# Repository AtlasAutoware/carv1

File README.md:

# carv1 — Atlas Autoware's first car

Everything for Atlas Autoware's first 1/10-scale autonomous race car in one
repo: the ROS 2 racing software, the Jetson setup that runs it, and the CAD
and electronics for the physical build. (The next car lives in
[carv2](https://github.com/AtlasAutoware/carv2).)

This repo combines two earlier ones, with their full commit history:
`atlasautoware` (the software, now the repo root) and `atlasautoware-cad`
(now [`cad/`](cad/)).

## What's where

| Path | What it holds |
|---|---|
| `f1tenth_gym_ros/`, `launch/`, `config/` | The ROS 2 racing stack: nodes, launch files, sim and car parameters |
| `racelines/`, `maps/` | Optimized racelines and track maps |
| `tools/`, `tests/`, `ui/`, `ml/`, `models/` | Tuning and benchmarking scripts, tests, the live dashboard, perception models |
| `hardware/` | What runs on the Jetson outside the ROS package: bringup scripts, udev rules, VESC config, race-day [RUNBOOK](hardware/RUNBOOK.md) |
| `docs/` | Design notes (MPC, racing tech, mapping, hardware wiring) and the project paper/report |
| `cad/Components/` | 3D models of the off-the-shelf parts (Jetson Orin Nano, RPLIDAR C1, PCA9685) |
| `cad/Mounts/` | Scripted (CadQuery) mounts and baseplate, with fit checks, fab exports and G-code — see [DESIGN.md](cad/Mounts/DESIGN.md) |
| `cad/Templates/` | The original clipless mounting system and baseplate the mounts are built on |
| `cad/Electronics/` | AtlasPower-4S, the power board that runs the car's electronics off the 4S drive pack — see its [README](cad/Electronics/README.md) |
| `cad/Jetson/` | JetPack rebuild and smoke-test scripts |

## The software stack

A complete ROS 2 racing stack for 1/10-scale autonomous racing: simulation
bridge, SLAM mapping, raceline optimization, an OSQP-based MPC racing
controller with lidar AEB and an IMU traction governor, camera opponent
detection, and a hardware bringup layer (Jetson + OAK-D Pro + RPLidar + VESC)
so the same nodes that win in sim drive the physical car.

Built on the [f1tenth_gym_ros](https://github.com/f1tenth/f1tenth_gym_ros)
simulation bridge (ROS 2 Humble).

```
                 ┌── sim:  gym_bridge (f1tenth_gym) ──────────────┐
sensors ─────────┤                                                ├──► /scan, odom, /oakd/*
                 └── car:  rplidar_node · oakd_camera · drive_node┘
                                            ▲
map ─► slam_toolbox ─► raceline_optimizer ─► raceline_mpc (MPC + AEB + traction governor) ─► /drive
                                            │
                       camera_perception ───┘ (YOLO opponent detection, optional)
```

## The racing pipeline

1. **Map** the track: `ros2 launch f1tenth_gym_ros slam_mapping_launch.py`
   driving slowly (or `mapping_driver` autonomously) — see
   [docs/mapping.md](docs/mapping.md).
2. **Optimize** a raceline: `raceline_optimizer` / `track_learner` produce
   `racelines/*.csv` (x, y, heading, curvature, speed); inspect with
   `tools/draw_raceline.py`.
3. **Profile** the speeds: `tools/reprofile_raceline.py` (or
   `reprofile_speeds: true` at runtime) replaces the speed column with the
   TUMFTM friction-limited forward-backward profile, so commanded speeds
   provably fit the grip budget — see
   [docs/racing_tech.md](docs/racing_tech.md).
4. **Race**: `raceline_mpc` tracks the line with a kinematic LTV-MPC
   (persistent warm-started OSQP solve, ~0.6 ms/tick), falls back to the
   MAP controller (Becker et al., ICRA 2023 — tire-aware pursuit) on any
   solver hiccup, brakes for obstacles with a speed-aware AEB, and scales
   speed when the IMU says grip is running out — see
   [docs/mpc.md](docs/mpc.md) and [docs/racing_tech.md](docs/racing_tech.md).

Racing nodes: `raceline_mpc` (competition time-trial), `race_agent` /
`racing_agent` (full strategy + opponents), `opponent_driver`,
`camera_perception` ([docs/camera_perception.md](docs/camera_perception.md)).
Tooling: `tools/auto_tune.py`, `tools/benchmark_lap.py`, and a live dashboard
([docs/dashboard.md](docs/dashboard.md)).

## Quickstart — simulation

Supported: Ubuntu 22.04 native with ROS 2 Humble, or any OS via Docker
(NVIDIA GPU with `rocker`, or noVNC without).

**Native (Ubuntu 22.04 + ROS 2 Humble):**
```bash
# dependencies
git clone https://github.com/f1tenth/f1tenth_gym && cd f1tenth_gym && pip3 install -e . && cd ..
# workspace
mkdir -p $HOME/sim_ws/src && cd $HOME/sim_ws/src
git clone https://github.com/AtlasAutoware/carv1 atlasautoware   # the paths below expect this folder name
# point map_path in config/sim.yaml at <your_home>/sim_ws/src/atlasautoware/maps/levine
cd $HOME/sim_ws
rosdep install -i --from-path src --rosdistro humble -y
colcon build
source /opt/ros/humble/setup.bash && source install/local_setup.bash
ros2 launch f1tenth_gym_ros gym_bridge_launch.py
```

**Docker (NVIDIA GPU):**
```bash
docker build -t f1tenth_gym_ros -f Dockerfile .
rocker --nvidia --x11 --volume .:/sim_ws/src/f1tenth_gym_ros -- f1tenth_gym_ros
```

**Docker (no GPU, noVNC):**
```bash
docker-compose up
# second terminal:
docker exec -it f1tenth_gym_ros-sim-1 /bin/bash
# browser: http://localhost:8080/vnc.html → Connect, then launch as above
```

Use `headless_bridge_launch.py` instead of `gym_bridge_launch.py` for
benchmarking/auto-tuning without rviz.

## Quickstart — real car

Jetson + OAK-D Pro (RGB + 200 Hz IMU) + RPLidar + VESC. Actuation goes
through a PCA9685 PWM board into the VESC's PPM input **or** direct VESC
UART — `drive_node` probes both at startup and uses what it finds:

```bash
pip3 install depthai rplidar-roboticia smbus2 pyserial
ros2 launch f1tenth_gym_ros car_bringup_launch.py
```

Install and compile the optional car detector once on the Jetson, then enable
it in bringup:

```bash
cd ~/atlas_ws/src/atlasautoware
hardware/scripts/install_tensorrt.sh
cd ~/atlas_ws
colcon build --packages-select f1tenth_gym_ros
source install/setup.bash
ros2 launch f1tenth_gym_ros car_bringup_launch.py use_perception:=true
```

Calibration (steering trim, `erpm_gain`, speed scaling) lives in
`config/hardware.yaml`. Wiring, VESC Tool setup, and the first-drive
calibration order are in [docs/hardware.md](docs/hardware.md). Both actuation
paths carry an arming hold, a command watchdog, and neutral-on-shutdown.
YOLO opponent detection uses a device-built TensorRT engine directly on the
Jetson GPU. The ONNX export is only an engine-build input; ONNX Runtime is not
loaded in the car process. See [docs/camera_perception.md](docs/camera_perception.md).

## Configuration

- `config/sim.yaml` — simulation: `map_path`, `num_agent` (1 or 2), start
  poses, `kb_teleop` (then `ros2 run teleop_twist_keyboard
  teleop_twist_keyboard`: `i`/`u`/`o` forward, `,`/`m`/`.` reverse, `k` stop).
- `config/hardware.yaml` — drive backend + sensor + racing parameters for the
  car.
- `config/slam_mapping.yaml` — mapping session settings.

## Topics

| Topic | Type | Direction |
|---|---|---|
| `/scan` | LaserScan | sim bridge / rplidar_node → stack |
| `/ego_racecar/odom` (sim) · `/pf/pose/odom` (car) | Odometry | localization → controllers |
| `/oakd/rgb`, `/oakd/camera_info` | Image, CameraInfo | oakd_camera → camera_perception |
| `/oakd/imu` | Imu | oakd_camera → traction governor |
| `/vesc/odom` | Odometry | drive_node (UART backend) → particle filter |
| `/drive` | AckermannDriveStamped | controllers → sim bridge / drive_node |
| `/map`, `tf` | — | map server / SLAM |

Two-agent sim additionally has `/opp_scan`, `/opp_drive`,
`/opp_racecar/odom`, and mirrored `opp_odom` topics; reset poses via RViz's
*2D Pose Estimate* (`/initialpose`) and *2D Goal Pose* tools.

## Tests

```bash
python3 -m pytest tests/ -q        # pure-logic: MPC, race brain, hardware drivers
python3 tests/test_mpc.py          # closed-loop MPC validation + solve-time budget
```

`tests/test_hardware.py` covers the PCA9685 register/pulse maths, the VESC
UART protocol, drive-backend auto-detection, lidar scan binning, and the
traction governor — no hardware or ROS needed.

## License

MIT — see [LICENSE](LICENSE).

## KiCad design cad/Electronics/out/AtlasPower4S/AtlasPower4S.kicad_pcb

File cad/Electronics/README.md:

# AtlasPower-4S

One board that runs the new car's electronics off the 4S drive LiPo, so the Baseus power
bank and the USB-C PD trigger come off the car entirely. 88 x 68 mm, four M3 holes on a
76 x 56 pattern, mounted on the clipless system by `../cad/power_board_mount.py`.

    XT90 -> 10 A fuse -> TVS -> ideal-diode FET -> 5 mohm shunt -> VIN
    VIN  -> AP64501 -> 10.0 V  Jetson Orin Nano + SICK TiM561
         -> AP64501 ->  7.4 V  INJORA INJS235 servo
         -> AP64501 ->  5.0 V  USB hub, PCA9685, fan
    INA226 across the shunt -> I2C -> Jetson

## Why these numbers

The pack is 12.0 V at a 3.0 V/cell cutoff and 16.8 V full. The Jetson takes 9-20 V and the
TiM561 takes 9-28 V, so both would run straight off the pack, and that is the tempting
wrong answer: the pack rail carries the motor's switching noise, and a hard launch sags it
far enough to brown out the Jetson mid-run.

The compute rail is therefore **10 V, not 12 V**. At 12 V a buck has no headroom left when
the pack is nearly flat and you need a buck-boost, which is a four-switch converter and a
much harder board. At 10 V a plain synchronous buck still has 0.8 V of headroom even at an
11 V sag, which is the single decision that keeps this board simple enough to get right.

Servo peaks are handled by a 470 uF reservoir rather than by sizing the regulator for
stall: a 35 kg-class servo pulls 3-6 A stalled but only for milliseconds, and sizing three
rails for simultaneous peaks would have pushed the board to 97 W and a lot of heat.

## Files

| file | what |
| --- | --- |
| `design.py` | every electrical number, and the checks over them. Run it first. |
| `netlist.py` | parts and nets, built from `design.py` |
| `gen_kicad.py` | writes the KiCad project from `netlist.py` |
| `gen_footprint.py` | the SRP1265A land pattern, from the datasheet drawing |
| `layout.py` | the floorplan and the copper plan, with the reasoning |
| `relax.py` | separates the floorplan until nothing overlaps |
| `place_check.py` | courtyard and edge checking from real footprint geometry |
| `gen_pcb.py` | writes the board: placement, zones, routing, via stitching |
| `libs/footprints/` | the 20 KiCad footprints this board uses, vendored so it builds anywhere |
| `out/AtlasPower4S/` | the KiCad project, schematic PDF, board, gerbers, drill, BOM, ERC/DRC |
| `../cad/power_board_mount.py` | the printed tray, on the clipless foot interface |

Regenerate everything:

    python3 design.py && python3 gen_footprint.py && python3 relax.py
    python3 place_check.py && python3 gen_kicad.py && python3 gen_pcb.py

## What has actually been verified

Everything below was run, not asserted:

- `design.py` passes all its checks: rail dividers land within 0.4 % of target on E96 pairs,
  the inductor is at or above minimum on every rail, saturation current clears 1.5x peak,
  every rail has headroom at an 11 V sag, and the shunt uses 49 % of the INA226's range
  without saturating it.
- The compensation values come from the AP64501 datasheet's own Eq. 17-20, and the method
  reproduces the datasheet's worked example (5 V, 5 A, 45 uF gives R5 = 15.8 k, as printed).
- KiCad parses the generated schematic and its extracted netlist matches `netlist.py`
  **exactly**: 42 nets, no missing, no extra, no membership differences.
- All 21 footprints resolve against the KiCad 10 libraries.
- 204 netlist pins, 204 global labels. BOM totals 84 parts against 84 in the netlist.
- ERC: **zero errors.** 84 warnings are `lib_symbol_issues`, which is `kicad-cli` not
  loading the project-local `sym-lib-table`; they disappear when the project is opened
  normally. 2 are `isolated_pin_label` on `ALERT` and `NC_VESC_5V`, both deliberate.

## The inductor footprint

Built by `gen_footprint.py` from the Bourns SRP1265A datasheet's Recommended Layout: 14.2 mm
overall span, 8.0 mm gap, 5.0 mm pad height, giving 3.1 mm pads at +-5.55 mm. Read off the
rendered drawing, not from extracted text, because extraction loses which number belongs to
which dimension line.

The reading confirms itself: 3.1 x 5.0 is exactly the part's worst-case terminal
(2.75 + 0.35 by 4.7 + 0.3), which is what a power-inductor land is. Had the 8.0 been
centre-to-centre rather than the gap, pads would have come out 6.2 mm wide against a 2.75 mm
terminal, which is not a land pattern anyone draws.

## The layout

4 layers: F.Cu components and local pours, In1.Cu solid ground, In2.Cu VIN distribution,
B.Cu ground and output pours. 88 x 68 mm, M3 holes on 76 x 56 to match the printed tray.

The board reads left to right in the order power flows: input protection, then the three
rail blocks stacked in y, then the output connectors. Each rail follows the AP64501
datasheet Figure 31 - input ceramics against VIN/GND, inductor immediately at SW, feedback
divider on the quiet side away from the switch node.

`layout.py` holds the hand floorplan (the intent: what sits next to what). `relax.py`
takes that as a seed and separates it numerically until no courtyard overlaps and nothing
crosses the board edge, because the hand coordinates were wrong in six places once the
footprints were real - a 1210 rotated 90 degrees has a 4.6 mm courtyard where I had written
3.4, and a terminal block's origin is pin 1 rather than its centre.

Routing is deliberate, not autorouted. Power nets are zones; signal nets get L-paths or a
perpendicular escape-and-return, each candidate checked against every pad of a different
net. **A connection that cannot be routed cleanly is left unrouted and reported rather than
shorted** - 20 of them currently, all in the dense compensation clusters.

### DRC status: honest

    659 violations on the first pass  ->  204 now

Fixed along the way, each one a real error: 54 courtyard overlaps, 4 parts hanging off the
board edge, 90 shorts from blind L-routing, 47 dangling vias, unfilled zones, the INA226's
exposed pad left unmapped, and library footprints whose built-in 0.2 mm thermal vias are
under the board's minimum hole size.

**What remains is a cleanup pass in the GUI, and the board should not be ordered until it is
done.** Roughly: 38 unconnected (the 20 unrouted signal connections above, plus ground
islands), 28 hole clearance and 25 shorts from ground vias placed too near other copper, 27
isolated copper regions and 25 starved thermals in the pours, and 25 `lib_footprint_mismatch`
which are benign - the footprints are emitted inline rather than linked to a library.

None of that is a design error; it is the last 10 % of a layout, which is the part a person
does with a mouse and the ratsnest visible. What the generator gives you is a board with
every part placed sensibly, every plane poured, the high-current paths done as copper rather
than traces, and a list of exactly what is left.

### Thermals

About 8 W total across three SO-8EP packages rated 45 C/W. Each exposed pad gets seven
stitching vias into the ground plane, which is what makes that 45 C/W figure meaningful.
Worth measuring on the first board rather than trusting.

Prices and stock were read from LCSC on 2026-09-07 and move.

## Two deliberate oddities

**J7 pin 2 is a dead net.** The VESC's PPM header carries 5 V, signal and ground. That 5 V
must never meet the servo BEC rail. The usual fix is "remember to pull the red pin from the
Y-lead", which is exactly the kind of instruction that gets forgotten once. Here the pin
physically goes nowhere, so the mistake is not available.

**The INA226 is powered from the Jetson's 3.3 V, not from a board rail.** Telemetry is
therefore only alive when the Jetson is, which is the correct dependency: there is nothing
to report to when it is off, and it keeps the sense chip off the noisy pack rail.

## Sources

- AP64501 datasheet DS41980 Rev. 5-2, Diodes Incorporated, December 2024 — pinout,
  0.8 V reference, 570 kHz, Eq. 6-20, Figure 31 layout guidance.
- LM74700-Q1 datasheet SNOSD17G, Texas Instruments — SOT-23-6 pinout, FET sizing rule.
- INA226 — 81.92 mV shunt full scale, 2.5 uV LSB.
- Jetson Orin Nano Developer Kit carrier board specification SP-11324-001 v1.1 — 9-20 V
  jack, 3.5 A rating.
- SICK TiM561-2050101 datasheet 1071419 — 9-28 V, external slow-blow fuse required.

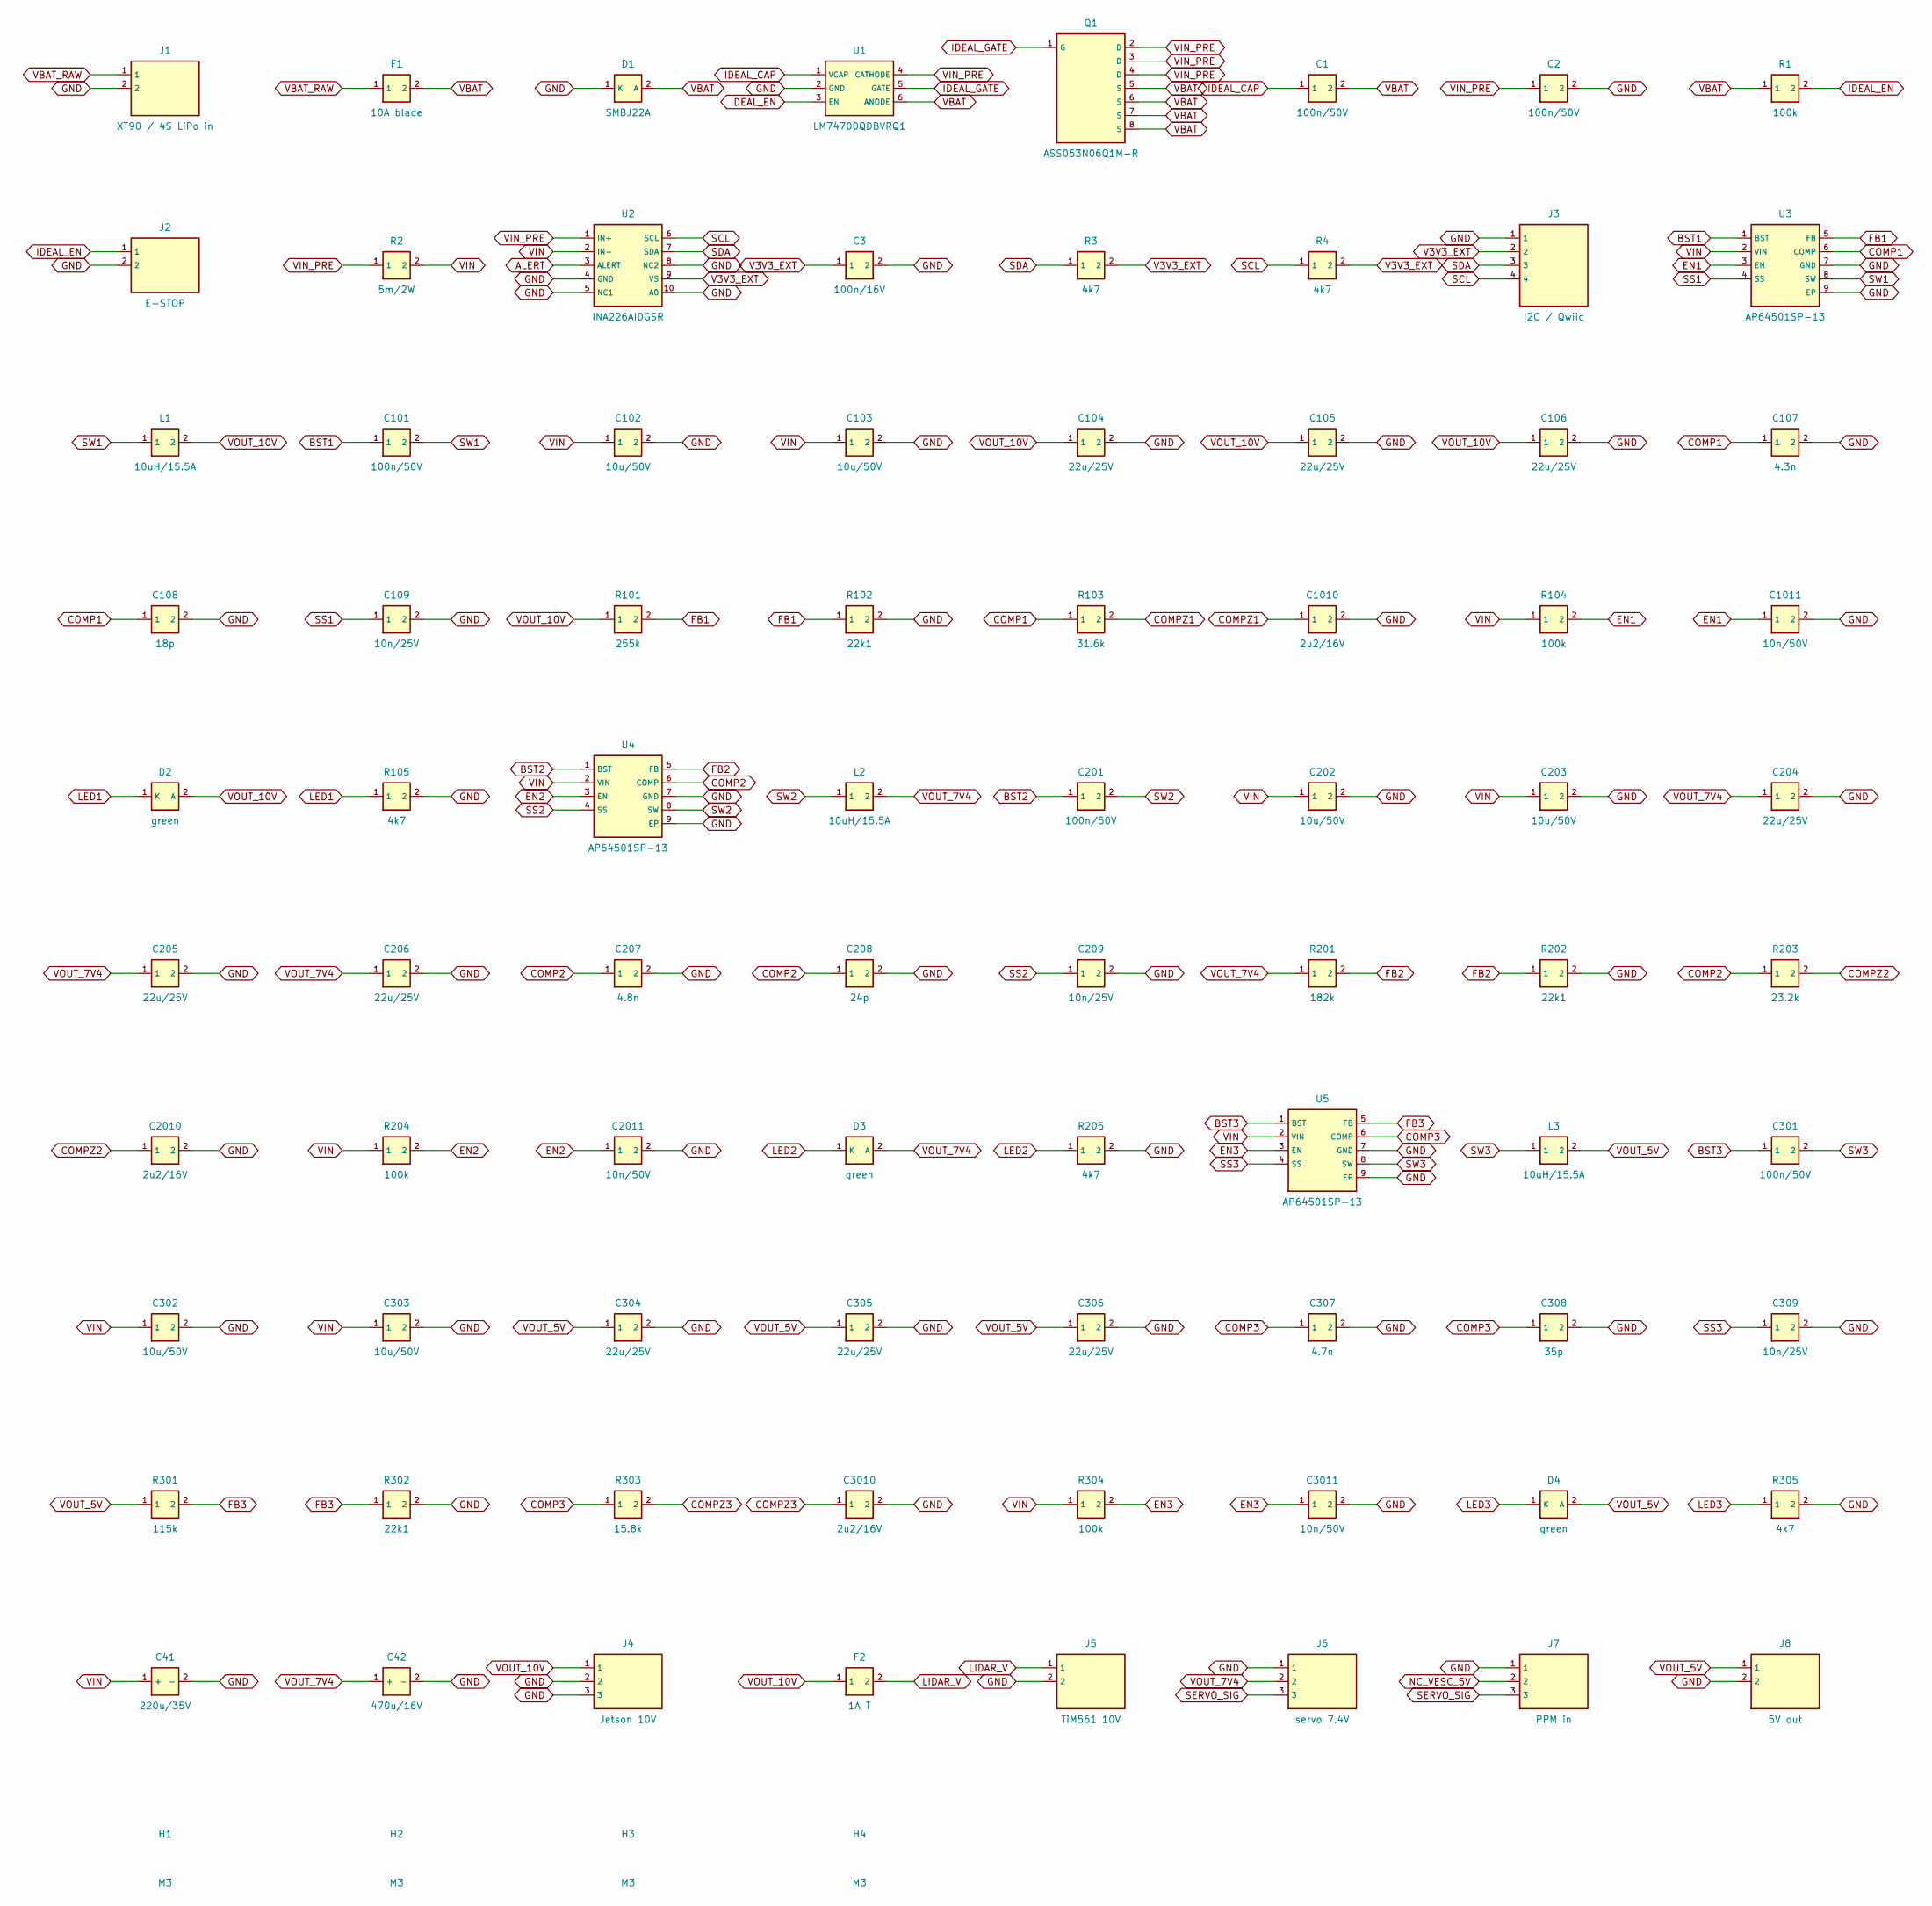
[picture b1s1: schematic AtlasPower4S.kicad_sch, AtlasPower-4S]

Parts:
C1, C2, C101, C201, C301: 100n/50V; C_0805_2012Metric
C3: 100n/16V; C_0805_2012Metric
C41: 220u/35V; CP_Elec_10x10.5
C42: 470u/16V; CP_Elec_10x10.5
C102, C103, C202, C203, C302, C303: 10u/50V; C_1210_3225Metric
C104, C105, C106, C204, C205, C206, C304, C305, C306: 22u/25V; C_1210_3225Metric
C107: 4.3n; C_0805_2012Metric
C108: 18p; C_0805_2012Metric
C109, C209, C309: 10n/25V; C_0805_2012Metric
C207: 4.8n; C_0805_2012Metric
C208: 24p; C_0805_2012Metric
C307: 4.7n; C_0805_2012Metric
C308: 35p; C_0805_2012Metric
C1010, C2010, C3010: 2u2/16V; C_0805_2012Metric
C1011, C2011, C3011: 10n/50V; C_0805_2012Metric
D1: SMBJ22A; D_SMB; LCSC C13964
D2, D3, D4: green; LED_0805_2012Metric
F1: 10A blade; Fuse_Blade_ATO_directSolder
F2: 1A T; Fuseholder_Clip-5x20mm_Keystone_3512P_Inline_P23.62x7.27mm_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
H1, H2, H3, H4: M3; MountingHole_3.2mm_M3
J1: XT90 / 4S LiPo in; TerminalBlock_Phoenix_MKDS-3-2-5.08_1x02_P5.08mm_Horizontal
J2: E-STOP; PinHeader_1x02_P2.54mm_Vertical
J3: I2C / Qwiic; JST_SH_SM04B-SRSS-TB_1x04-1MP_P1.00mm_Horizontal
J4: Jetson 10V; BarrelJack_Horizontal
J5: TiM561 10V; TerminalBlock_Phoenix_MKDS-1,5-2-5.08_1x02_P5.08mm_Horizont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
J6: servo 7.4V; PinHeader_1x03_P2.54mm_Vertical
J7: PPM in; PinHeader_1x03_P2.54mm_Vertical
J8: 5V out; TerminalBlock_Phoenix_MKDS-1,5-2-5.08_1x02_P5.08mm_Horizont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
L1, L2, L3: 10uH/15.5A; L_Bourns_SRP1265A; MPN SRP1265A-100M; LCSC C840531
Q1: ASS053N06Q1M-R; PowerPAK_SO-8_Single; MPN ASS053N06Q1M-R; LCSC C53896939
R1, R104, R204, R304: 100k; R_0805_2012Metric
R2: 5m/2W; R_2512_6332Metric; LCSC C2962780
R3, R4, R105, R205, R305: 4k7; R_0805_2012Metric
R101: 255k; R_0805_2012Metric
R102, R202, R302: 22k1; R_0805_2012Metric
R103: 31.6k; R_0805_2012Metric
R201: 182k; R_0805_2012Metric
R203: 23.2k; R_0805_2012Metric
R301: 115k; R_0805_2012Metric
R303: 15.8k; R_0805_2012Metric
U1: LM74700QDBVRQ1; SOT-23-6; MPN LM74700QDBVRQ1; LCSC C2941042
U2: INA226AIDGSR; MSOP-10-1EP_3x3mm_P0.5mm_EP1.68x1.88mm; MPN INA226AIDGSR; LCSC C49851
U3, U4, U5: AP64501SP-13; SOIC-8-1EP_3.9x4.9mm_P1.27mm_EP2.29x3mm; MPN AP64501SP-13; LCSC C2071517

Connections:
ALERT: U2.3 (ALERT)
BST1: C101.1, U3.1 (BST)
BST2: C201.1, U4.1 (BST)
BST3: C301.1, U5.1 (BST)
COMP1: C107.1, C108.1, R103.1, U3.6 (COMP)
COMP2: C207.1, C208.1, R203.1, U4.6 (COMP)
COMP3: C307.1, C308.1, R303.1, U5.6 (COMP)
COMPZ1: C1010.1, R103.2
COMPZ2: C2010.1, R203.2
COMPZ3: C3010.1, R303.2
EN1: C1011.1, R104.2, U3.3 (EN)
EN2: C2011.1, R204.2, U4.3 (EN)
EN3: C3011.1, R304.2, U5.3 (EN)
FB1: R101.2, R102.1, U3.5 (FB)
FB2: R201.2, R202.1, U4.5 (FB)
FB3: R301.2, R302.1, U5.5 (FB)
GND: C2.2, C3.2, C41.2 (-), C42.2 (-), C102.2, C103.2, C104.2, C105.2, C106.2, C107.2, C108.2, C109.2, C202.2, C203.2, C204.2, C205.2, C206.2, C207.2, C208.2, C209.2, C302.2, C303.2, C304.2, C305.2, C306.2, C307.2, C308.2, C309.2, C1010.2, C1011.2, C2010.2, C2011.2, C3010.2, C3011.2, D1.1 (K), J1.2, J2.2, J3.1, J4.2, J4.3, J5.2, J6.1, J7.1, J8.2, R102.2, R105.2, R202.2, R205.2, R302.2, R305.2, U1.2 (GND), U2.4 (GND), U2.5 (NC1), U2.8 (NC2), U2.10 (A0), U2.11, U3.7 (GND), U3.9 (EP), U4.7 (GND), U4.9 (EP), U5.7 (GND), U5.9 (EP)
IDEAL_CAP: C1.1, U1.1 (VCAP)
IDEAL_EN: J2.1, R1.2, U1.3 (EN)
IDEAL_GATE: Q1.1 (G), U1.5 (GATE)
LED1: D2.1 (K), R105.1
LED2: D3.1 (K), R205.1
LED3: D4.1 (K), R305.1
LIDAR_V: F2.2, J5.1
NC_VESC_5V: J7.2
SCL: J3.4, R4.1, U2.6 (SCL)
SDA: J3.3, R3.1, U2.7 (SDA)
SERVO_SIG: J6.3, J7.3
SS1: C109.1, U3.4 (SS)
SS2: C209.1, U4.4 (SS)
SS3: C309.1, U5.4 (SS)
SW1: C101.2, L1.1, U3.8 (SW)
SW2: C201.2, L2.1, U4.8 (SW)
SW3: C301.2, L3.1, U5.8 (SW)
V3V3_EXT: C3.1, J3.2, R3.2, R4.2, U2.9 (VS)
VBAT: C1.2, D1.2 (A), F1.2, Q1.5 (S), Q1.6 (S), Q1.7 (S), Q1.8 (S), R1.1, U1.6 (ANODE)
VBAT_RAW: F1.1, J1.1
VIN: C41.1 (+), C102.1, C103.1, C202.1, C203.1, C302.1, C303.1, R2.2, R104.1, R204.1, R304.1, U2.2 (IN-), U3.2 (VIN), U4.2 (VIN), U5.2 (VIN)
VIN_PRE: C2.1, Q1.2 (D), Q1.3 (D), Q1.4 (D), R2.1, U1.4 (CATHODE), U2.1 (IN+)
VOUT_5V: C304.1, C305.1, C306.1, D4.2 (A), J8.1, L3.2, R301.1
VOUT_7V4: C42.1 (+), C204.1, C205.1, C206.1, D3.2 (A), J6.2, L2.2, R201.1
VOUT_10V: C104.1, C105.1, C106.1, D2.2 (A), F2.1, J4.1, L1.2, R101.1

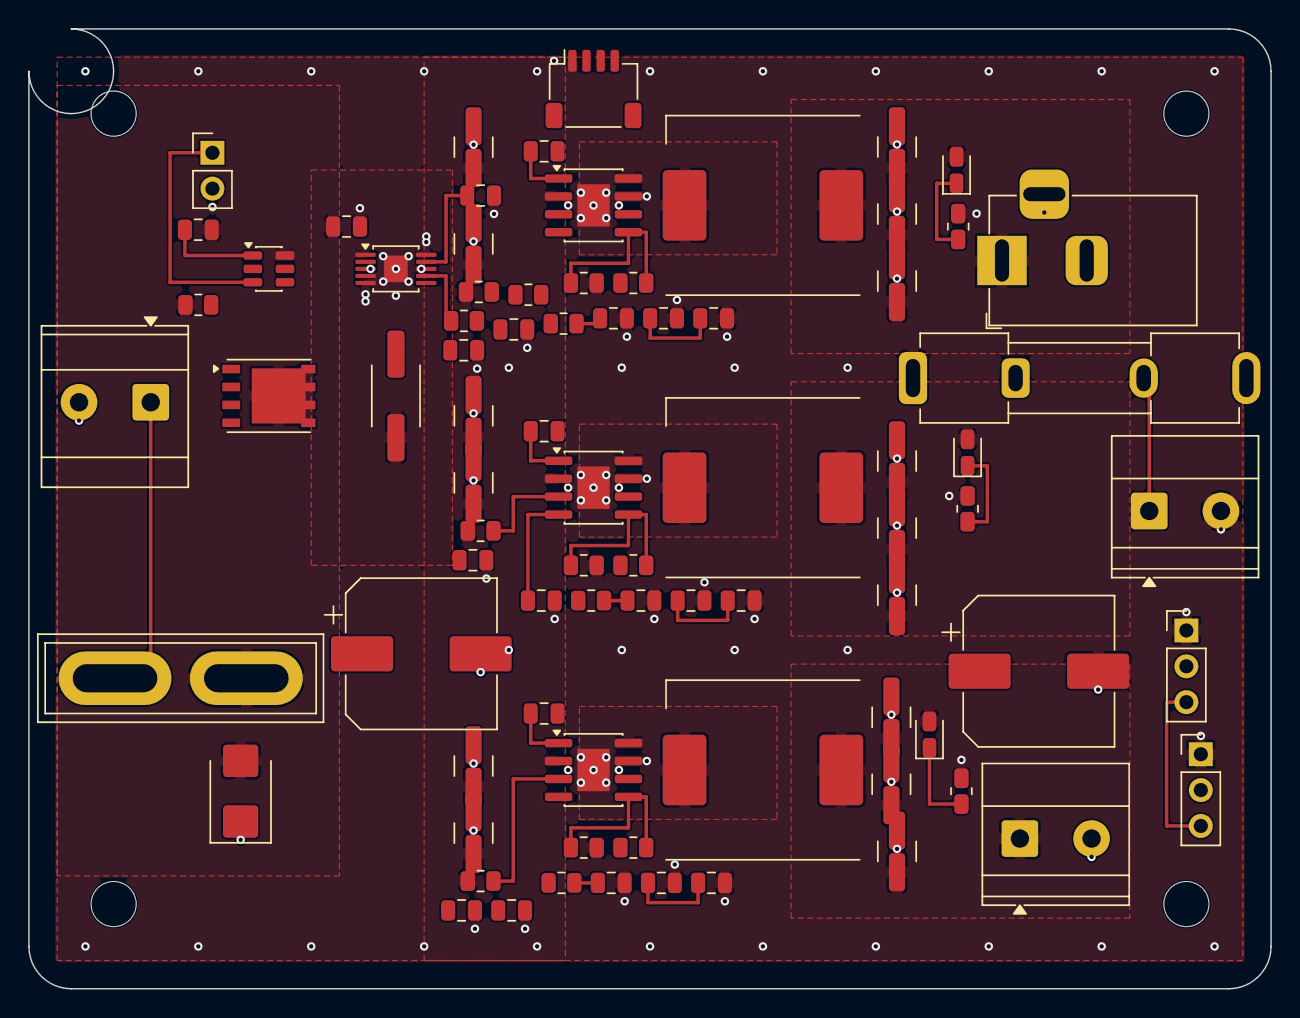
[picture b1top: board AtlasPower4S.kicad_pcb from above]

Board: 4 copper layers, 88.0 x 68.0 mm, 84 parts (0 on the bottom side), 40 nets.

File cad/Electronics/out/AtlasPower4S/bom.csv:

"Reference","Value","Footprint","MPN","LCSC","Description","QUANTITY"
"C1,C2,C101,C201,C301","100n/50V","Capacitor_SMD:C_0805_2012Metric","","","LM74700 cathode bypass,LM74700 charge-pump cap,bootstrap, datasheet 100 nF","5"
"C3","100n/16V","Capacitor_SMD:C_0805_2012Metric","","","INA226 supply bypass","1"
"C41","220u/35V","Capacitor_SMD:CP_Elec_10x10.5","","","input bulk","1"
"C42","470u/16V","Capacitor_SMD:CP_Elec_10x10.5","","","servo stall reservoir","1"
"C102,C103,C202,C203,C302,C303","10u/50V","Capacitor_SMD:C_1210_3225Metric","","","input ceramic","6"
"C104-C106,C204-C206,C304-C306","22u/25V","Capacitor_SMD:C_1210_3225Metric","","","output ceramic","9"
"C107","4.3n","Capacitor_SMD:C_0805_2012Metric","","","loop zero, Eq. 18","1"
"C108","18p","Capacitor_SMD:C_0805_2012Metric","","","loop pole, Eq. 19","1"
"C109,C209,C309","10n/25V","Capacitor_SMD:C_0805_2012Metric","","","soft start, 4 ms","3"
"C207","4.8n","Capacitor_SMD:C_0805_2012Metric","","","loop zero, Eq. 18","1"
"C208","24p","Capacitor_SMD:C_0805_2012Metric","","","loop pole, Eq. 19","1"
"C307","4.7n","Capacitor_SMD:C_0805_2012Metric","","","loop zero, Eq. 18","1"
"C308","35p","Capacitor_SMD:C_0805_2012Metric","","","loop pole, Eq. 19","1"
"C1010,C2010,C3010","2u2/16V","Capacitor_SMD:C_0805_2012Metric","","","loop series cap","3"
"C1011,C2011,C3011","10n/50V","Capacitor_SMD:C_0805_2012Metric","","","stagger start, ~8 ms apart","3"
"D1","SMBJ22A","Diode_SMD:D_SMB","","C13964","TVS, 22 V standoff, clamps motor regen","1"
"D2-D4","green","LED_SMD:LED_0805_2012Metric","","","rail present","3"
"F1","10A blade","Fuse:Fuse_Blade_ATO_directSolder","","","ATO blade, the one user-serviceable fuse","1"
"F2","1A T","Fuse:Fuseholder_Clip-5x20mm_Keystone_3512P_Inline_P23.62x7.27mm_D1.02x2.41x1.02x1.57mm_Horizontal","","","SICK requires an external slow-blow on the lidar","1"
"H1-H4","M3","MountingHole:MountingHole_3.2mm_M3","","","","4"
"J1","XT90 / 4S LiPo in","TerminalBlock_Phoenix:TerminalBlock_Phoenix_MKDS-3-2-5.08_1x02_P5.08mm_Horizontal","","","pack input, 24 A rated block","1"
"J2","E-STOP","Connector_PinHeader_2.54mm:PinHeader_1x02_P2.54mm_Vertical","","","short to kill every rail; leave open to run","1"
"J3","I2C / Qwiic","Connector_JST:JST_SH_SM04B-SRSS-TB_1x04-1MP_P1.00mm_Horizontal","","","to the Jetson 40-pin header: 3.3 V, SDA, SCL, GND","1"
"J4","Jetson 10V","Connector_BarrelJack:BarrelJack_Horizontal","","","5.5 x 2.5 mm centre positive","1"
"J5","TiM561 10V","TerminalBlock_Phoenix:TerminalBlock_Phoenix_MKDS-1,5-2-5.08_1x02_P5.08mm_Horizontal","","","M12 brown = pin 1 +V, blue = pin 3 0 V","1"
"J6","servo 7.4V","Connector_PinHeader_2.54mm:PinHeader_1x03_P2.54mm_Vertical","","","V+ and GND from this board; signal passes through from the VESC PPM header","1"
"J7","PPM in","Connector_PinHeader_2.54mm:PinHeader_1x03_P2.54mm_Vertical","","","from the VESC. Pin 2 is deliberately a dead net: the VESC 5 V must not meet the BEC rail, which is the mistake this connector exists to prevent","1"
"J8","5V out","TerminalBlock_Phoenix:TerminalBlock_Phoenix_MKDS-1,5-2-5.08_1x02_P5.08mm_Horizontal","","","USB hub / PCA9685 / fan","1"
"L1-L3","10uH/15.5A","Inductor_SMD:L_APV_APH1265","SRP1265A-100M","C840531","shielded power inductor","3"
"Q1","ASS053N06Q1M-R","Package_SO:PowerPAK_SO-8_Single","ASS053N06Q1M-R","C53896939","60 V 5.5 mohm N-FET, source to pack, drain to load","1"
"R1,R104,R204,R304","100k","Resistor_SMD:R_0805_2012Metric","","","enable pull-up to VIN,ideal-diode enable pull-up","4"
"R2","5m/2W","Resistor_SMD:R_2512_6332Metric","","C2962780","INA226 shunt, 40 mV at 8 A","1"
"R3,R4,R105,R205,R305","4k7","Resistor_SMD:R_0805_2012Metric","","","I2C pull-up,LED series","5"
"R101","255k","Resistor_SMD:R_0805_2012Metric","","","feedback top","1"
"R102,R202,R302","22k1","Resistor_SMD:R_0805_2012Metric","","","feedback bottom","3"
"R103","31.6k","Resistor_SMD:R_0805_2012Metric","","","loop resistor, Eq. 17","1"
"R201","182k","Resistor_SMD:R_0805_2012Metric","","","feedback top","1"
"R203","23.2k","Resistor_SMD:R_0805_2012Metric","","","loop resistor, Eq. 17","1"
"R301","115k","Resistor_SMD:R_0805_2012Metric","","","feedback top","1"
"R303","15.8k","Resistor_SMD:R_0805_2012Metric","","","loop resistor, Eq. 17","1"
"U1","LM74700QDBVRQ1","Package_TO_SOT_SMD:SOT-23-6","LM74700QDBVRQ1","C2941042","ideal diode controller, reverse battery","1"
"U2","INA226AIDGSR","Package_SO:MSOP-10-1EP_3x3mm_P0.5mm_EP1.68x1.88mm_ThermalVias","INA226AIDGSR","C49851","pack voltage + current telemetry","1"
"U3-U5","AP64501SP-13","Package_SO:SOIC-8-1EP_3.9x4.9mm_P1.27mm_EP2.29x3mm_ThermalVias","AP64501SP-13","C2071517","synchronous buck, 10.0 V at 3.3 A,synchronous buck, 5.0 V at 3.0 A,synchronous buck, 7.4 V at 3.0 A","3"
